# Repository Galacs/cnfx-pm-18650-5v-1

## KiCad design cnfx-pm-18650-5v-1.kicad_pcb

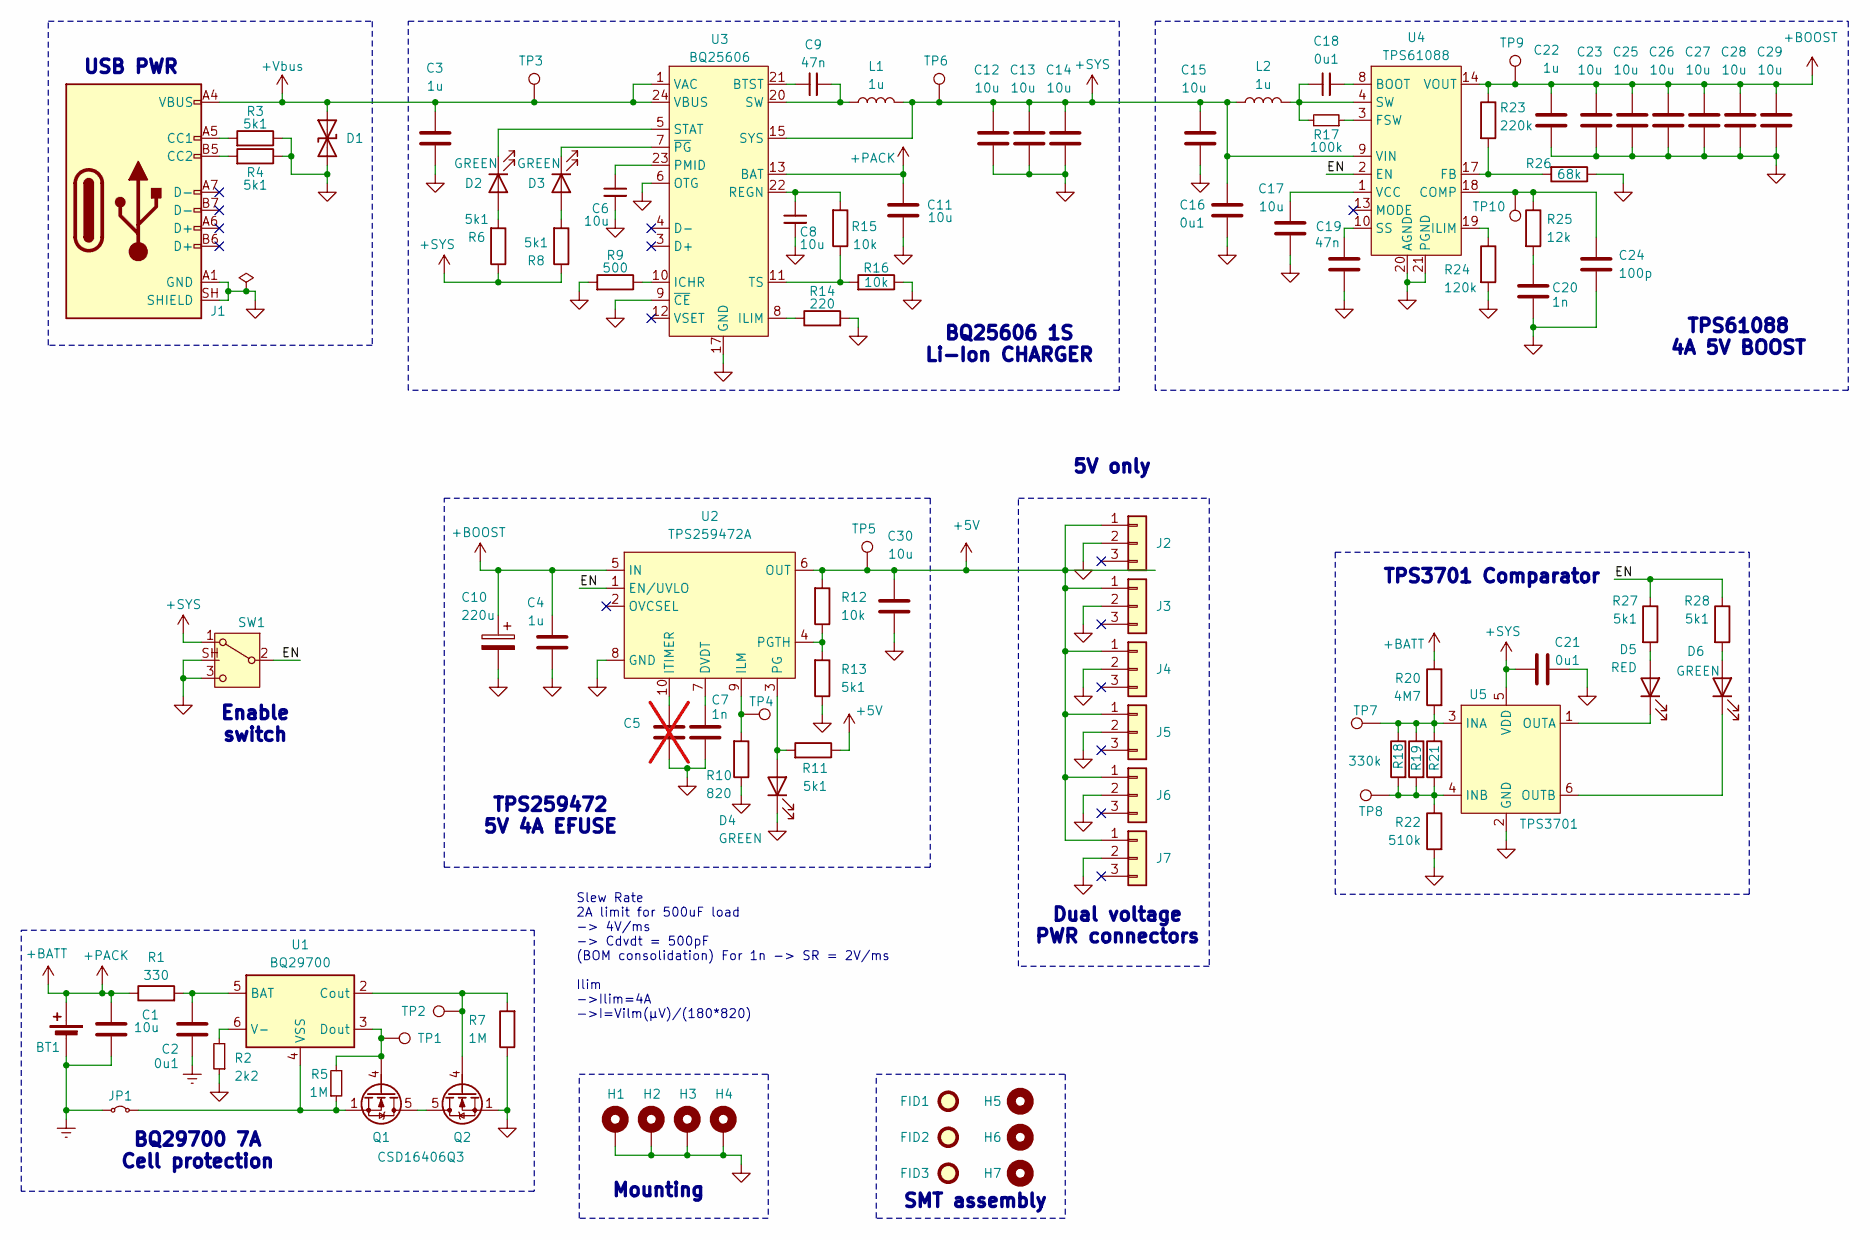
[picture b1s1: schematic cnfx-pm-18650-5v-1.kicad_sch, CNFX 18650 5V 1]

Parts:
BT1: Battery_Cell; BatteryHolder_MYOUNG_BH-18650-B1BA002
C1, C6, C8, C11, C12, C13, C14, C15, C17, C23, C25, C26, C27, C28, C29, C30: 10u; C_0603_1608Metric; Manufacturer Part Number CL10A106KP8NNNC; JLCPCB Part # C19702
C2, C16, C18, C21: 0u1; C_0402_1005Metric; Manufacturer Part Number CL05B104KB54PNC; JLCPCB Part # C307331
C3, C4, C22: 1u; C_0402_1005Metric; Manufacturer Part Number CL05A105KA5NQNC; JLCPCB Part # C52923
C5: C; C_0402_1005Metric; not fitted
C7, C20: 1n; C_0402_1005Metric; Manufacturer Part Number 0402B102K500NT; JLCPCB Part # C1523
C9, C19: 47n; C_0603_1608Metric; Manufacturer Part Number CL10B473KB8NNNC; JLCPCB Part # C1622
C10: 220u; CP_Elec_6.3x7.7; Manufacturer Part Number RVT1E221M0607; JLCPCB Part # C2918361
C24: 100p; C_0402_1005Metric; Manufacturer Part Number 0402CG101J500NT; JLCPCB Part # C1546
D1: SMBJ6.0CA; D_SMB; Manufacturer Part Number SMBJ6.0CA; JLCPCB Part # C2925451
D2, D3, D4, D6: GREEN; LED_0805_2012Metric; Manufacturer Part Number KT-0805G; JLCPCB Part # C2297
D5: RED; LED_0805_2012Metric; Manufacturer Part Number NCD0805R1; JLCPCB Part # C84256
FID1, FID2, FID3: Fiducial; Fiducial_1mm_Mask2mm
H1, H2, H3, H4: MountingHole_Pad; MountingHole_3.2mm_M3_Pad_Via
H5, H6, H7: MountingHole; ToolingHole_1.152mm
J1: USB_C_Receptacle_USB2.0_14P; USB_C_Receptacle_HRO_TYPE-C-31-M-12; Manufacturer Part Number TYPE-C16PIN; JLCPCB Part # C393939
J2, J3, J4, J5, J6, J7: Conn_01x03; JST_XH_B3B-XH-A_1x03_P2.50mm_Vertical; Manufacturer Part Number B3B-XH-A(LF)(SN); JLCPCB Part # C144394
JP1: Jumper_2_Small_Bridged; PinHeader_1x02_P2.54mm_Vertical
L1, L2: 1u; L_APV_APH0530; Manufacturer Part Number MCMB-0530-1R0MT; JLCPCB Part # C18222176
Q1, Q2: CSD16406Q3; VSON-8_3.3x3.3mm_P0.65mm_NexFET; Manufacturer Part Number CSD16406Q3; JLCPCB Part # C2861720
R1: 330; R_0402_1005Metric; Manufacturer Part Number 0402WGF3300TCE; JLCPCB Part # C25104
R2: 2k2; R_0402_1005Metric; Manufacturer Part Number 0402WGF2201TCE; JLCPCB Part # C25879
R3, R4, R6, R8, R11, R13, R27, R28: 5k1; R_0402_1005Metric; Manufacturer Part Number 0402WGF5101TCE; JLCPCB Part # C25905
R5, R7: 1M; R_0402_1005Metric; Manufacturer Part Number 0402WGF1004TCE; JLCPCB Part # C26083
R9: 500; R_0402_1005Metric; Manufacturer Part Number 0402WGF5100TCE; JLCPCB Part # C25123
R10: 820; R_0402_1005Metric; Manufacturer Part Number 0402WGF8200TCE; JLCPCB Part # C25135
R12, R15, R16: 10k; R_0402_1005Metric; Manufacturer Part Number 0402WGF1002TCE; JLCPCB Part # C25744
R14: 220; R_0402_1005Metric; Manufacturer Part Number 0402WGF2200TCE; JLCPCB Part # C25091
R17: 100k; R_0402_1005Metric; Manufacturer Part Number 0402WGF1003TCE; JLCPCB Part # C25741
R18, R19, R21: 330k; R_0603_1608Metric; Manufacturer Part Number 0603WAF3303T5E; JLCPCB Part # C23137
R20: 4M7; R_0603_1608Metric; Manufacturer Part Number 0603WAF4704T5E; JLCPCB Part # C23163
R22: 510k; R_0603_1608Metric; Manufacturer Part Number 0603WAF5103T5E; JLCPCB Part # C23192
R23: 220k; R_0603_1608Metric; Manufacturer Part Number 0603WAF2203T5E; JLCPCB Part # C22961
R24: 120k; R_0603_1608Metric; Manufacturer Part Number 0603WAF1203T5E; JLCPCB Part # C25808
R25: 12k; R_0402_1005Metric; Manufacturer Part Number 0402WGF1202TCE; JLCPCB Part # C25752
R26: 68k; R_0603_1608Metric; Manufacturer Part Number 0603WAF6802T5E; JLCPCB Part # C23231
SW1: SW_SPDT; SW_SPDT_Shouhan_MSK12C02; Manufacturer Part Number MSK12C02; JLCPCB Part # C431540
TP1, TP2, TP3, TP4, TP5, TP6, TP7, TP8, TP9, TP10: TestPoint; TestPoint_Pad_D1.0mm
U1: BQ29700; WSON-6_1.5x1.5mm_P0.5mm; Manufacturer Part Number BQ29700DSER; JLCPCB Part # C183096
U2: TPS259472A; Texas_RPW0010A_VQFN-HR-10_2x2mm_P0.5mm; Manufacturer Part Number TPS259472ARPWR; JLCPCB Part # C3662789
U3: BQ25606; Texas_RGE0024H_VQFN-24-1EP_4x4mm_P0.5mm_EP2.7x2.7mm_Thermal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; Manufacturer Part Number BQ25606RGER; JLCPCB Part # C374063
U4: TPS61088; Texas_VQFN-RHL-20_ThermalVias; Manufacturer Part Number TPS61088RHLR; JLCPCB Part # C87357
U5: TPS3701; TSOT-23-6; Manufacturer Part Number TPS3701DDCR; JLCPCB Part # C132788

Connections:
+5V: C30.1, J2.1, J3.1, J4.1, J5.1, J6.1, J7.1, R11.1, R12.2, TP5.1 (1_1), U2.6 (OUT)
+BATT: BT1.1 (+), C1.1, C11.1, R1.1, R20.1, U3.13 (BAT), U3.14 (BAT)
+BOOST: C4.2, C10.1, C22.2, C23.1, C25.1, C26.1, C27.1, C28.1, C29.1, R23.1, TP9.1 (1_1), U2.5 (IN), U4.14 (VOUT), U4.15 (VOUT), U4.16 (VOUT)
+SYS: C12.1, C13.1, C14.1, C15.1, C16.1, C21.2, L1.2, L2.1, R6.1, R8.1, SW1.1 (A), TP6.1 (1_1), U3.15 (SYS), U3.16 (SYS), U4.9 (VIN), U5.5 (VDD)
+Vbus: C3.2, D1.1 (A1), J1.A4 (VBUS), J1.A9 (VBUS), J1.B4 (VBUS), J1.B9 (VBUS), TP3.1 (1_1), U3.1 (VAC), U3.24 (VBUS)
/EN: R27.1, R28.1, SW1.2 (B), U2.1 (EN/UVLO), U4.2 (EN)
GND: C3.1, C4.1, C5.2, C6.1, C7.2, C8.2, C10.2, C11.2, C12.2, C13.2, C14.2, C15.2, C16.2, C17.2, C19.1, C20.2, C21.1, C22.1, C23.2, C24.2, C25.2, C26.2, C27.2, C28.2, C29.2, C30.2, D1.2 (A2), D4.1 (K), H1.1 (1_1), H2.1 (1_1), H3.1 (1_1), H4.1 (1_1), J1.A1 (GND), J1.A12 (GND), J1.B1 (GND), J1.B12 (GND), J1.SH (SHIELD), J2.2, J3.2, J4.2, J5.2, J6.2, J7.2, Q2.1 (S), Q2.2 (S), Q2.3 (S), R2.1, R3.1, R4.1, R7.1, R9.2, R10.1, R13.1, R14.2, R16.1, R22.2, R24.2, R26.1, SW1.3 (C), SW1.SH, U2.8 (GND), U3.6 (OTG), U3.9 (~CE), U3.17 (GND), U3.18 (GND), U3.25 (PAD), U4.11 (NC), U4.12 (NC), U4.20 (AGND), U4.21 (PGND), U5.2 (GND)
unnamed: C9.2, L1.1, U3.19 (SW), U3.20 (SW)
unnamed: C18.1, L2.2, R17.2, U4.4 (SW), U4.5 (SW), U4.6 (SW), U4.7 (SW)
unnamed: C20.1, R25.2
unnamed: D2.2 (A), R6.2
unnamed: D2.1 (K), U3.5 (STAT)
unnamed: D3.2 (A), R8.2
unnamed: D3.1 (K), U3.7 (~PG)
unnamed: D4.2 (A), R11.2, U2.3 (PG)
unnamed: D5.2 (A), R27.2
unnamed: D5.1 (K), U5.1 (OUTA)
unnamed: D6.2 (A), R28.2
unnamed: D6.1 (K), U5.6 (OUTB)
unnamed: J1.A5 (CC1), R3.2
unnamed: J1.B5 (CC2), R4.2
unnamed: Q1.5 (D), Q2.5 (D)
unnamed: Q1.4 (G), R5.2, TP1.1 (1_1), U1.3 (Dout)
unnamed: Q2.4 (G), R7.2, TP2.1 (1_1), U1.2 (Cout)
unnamed: C2.2, R1.2, U1.5 (BAT)
unnamed: R2.2, U1.6 (V-)
unnamed: C7.1, U2.7 (DVDT)
unnamed: R10.2, TP4.1 (1_1), U2.9 (ILM)
unnamed: C5.1, U2.10 (ITIMER)
unnamed: R12.1, R13.2, U2.4 (PGTH)
unnamed: C9.1, U3.21 (BTST)
unnamed: R9.1, U3.10 (ICHR)
unnamed: R14.1, U3.8 (ILIM)
unnamed: C6.2, U3.23 (PMID)
unnamed: C8.1, R15.2, U3.22 (REGN)
unnamed: R15.1, R16.2, U3.11 (TS)
unnamed: C18.2, U4.8 (BOOT)
unnamed: C24.1, R25.1, TP10.1 (1_1), U4.18 (COMP)
unnamed: R23.2, R26.2, U4.17 (FB)
unnamed: R17.1, U4.3 (FSW)
unnamed: R24.1, U4.19 (ILIM)
unnamed: C19.2, U4.10 (SS)
unnamed: C17.1, U4.1 (VCC)
unnamed: R18.1, R19.1, R20.2, R21.1, TP7.1 (1_1), U5.3 (INA)
unnamed: R18.2, R19.2, R21.2, R22.1, TP8.1 (1_1), U5.4 (INB)

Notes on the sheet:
Enable switch
BQ29700 7A Cell protection
Slew Rate 2A limit for 500uF load -> 4V/ms -> Cdvdt = 500pF (BOM consolidation) For 1n -> SR = 2V/ms Ilim ->Ilim=4A ->I=Vilm(µV)/(180*820)
TPS259472 5V 4A EFUSE
5V only
Mounting
SMT assembly
USB PWR
TPS61088 4A 5V BOOST
BQ25606 1S Li-Ion CHARGER
Dual voltage PWR connectors
TPS3701 Comparator

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
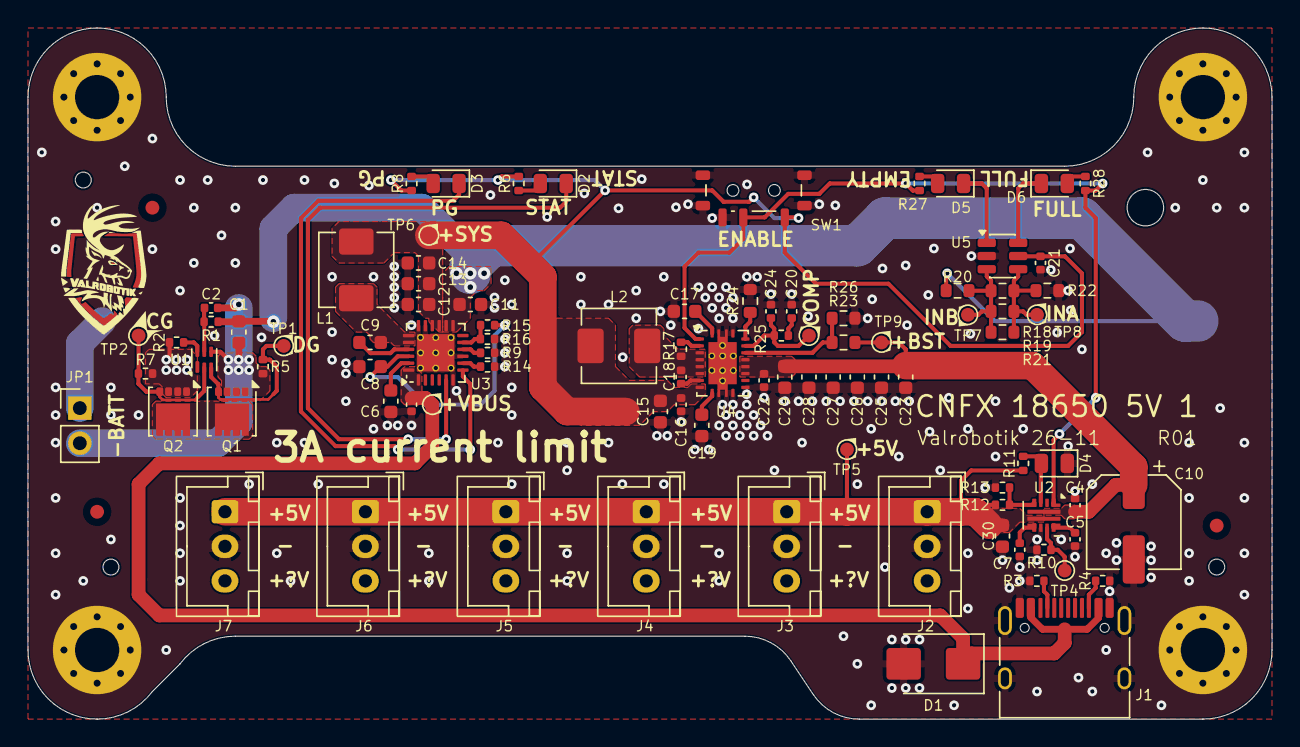
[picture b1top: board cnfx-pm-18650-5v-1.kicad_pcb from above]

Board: 2 copper layers, 90.0 x 50.0 mm, 103 parts (1 on the bottom side), 46 nets.

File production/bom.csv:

Designator,Footprint,Quantity,Value,LCSC Part #
"C1, C11, C12, C13, C14, C15, C17, C23, C25, C26, C27, C28, C29, C30, C6, C8",0603,16,10u,C19702
C10,CP_Elec_6.3x7.7,1,220u,C2918361
"C16, C18, C2, C21",0402,4,0u1,C307331
"C19, C9",0603,2,47n,C1622
"C20, C7",0402,2,1n,C1523
"C22, C3, C4",0402,3,1u,C52923
C24,0402,1,100p,C1546
D1,D_SMB,1,SMBJ6.0CA,C2925451
"D2, D3, D4, D6",0805,4,GREEN,C2297
D5,0805,1,RED,NCD0805R1
J1,USB_C_Receptacle_HRO_TYPE-C-31-M-12,1,USB_C_Receptacle_USB2.0_14P,C393939
"J2, J3, J4, J5, J6, J7",JST_XH_B3B-XH-A_1x03_P2.50mm_Vertical,6,Conn_01x03,C144394
"L1, L2",L_APV_APH0530,2,1u,C18222176
"Q1, Q2",VSON-8_3.3x3.3mm_P0.65mm_NexFET,2,CSD16406Q3,C2861720
R1,0402,1,330,C25104
R10,0402,1,820,C25135
"R11, R13, R27, R28, R3, R4, R6, R8",0402,8,5k1,C25905
"R12, R15, R16",0402,3,10k,C25744
R14,0402,1,220,C25091
R17,0402,1,100k,C25741
"R18, R19, R21",0603,3,330k,C23137
R2,0402,1,2k2,C25879
R20,0603,1,4M7,C23163
R22,0603,1,510k,C23192
R23,0603,1,220k,C22961
R24,0603,1,120k,C25808
R25,0402,1,12k,C25752
R26,0603,1,68k,C23231
"R5, R7",0402,2,1M,C26083
R9,0402,1,500,C25123
SW1,SW_SPDT_Shouhan_MSK12C02,1,SW_SPDT,C431540
U1,WSON-6_1.5x1.5mm_P0.5mm,1,BQ29700,C183096
U2,Texas_RPW0010A_VQFN-HR-10_2x2mm_P0.5mm,1,TPS259472A,C3662789
U3,Texas_RGE0024H_VQFN-24-1EP_4x4mm_P0.5mm_EP2.7x2.7mm_ThermalVias,1,BQ25606,C374063
U4,Texas_VQFN-RHL-20_ThermalVias,1,TPS61088,C87357
U5,TSOT-23-6,1,TPS3701,C132788
